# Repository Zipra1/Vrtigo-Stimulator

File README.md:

# This project is very very new, there is like. nothing here yet. Come back later?
GVS stimulation device, primarily for use in Virtual Reality applications (such as VRChat) to provide a sense of movement when you are moved in the game. Could also theoretically be used to reduce motion sickness, but the main goal is haptics.
Eventually, there will be two more repos: `Vertigo-Receiver` and `Vertigo-Server`

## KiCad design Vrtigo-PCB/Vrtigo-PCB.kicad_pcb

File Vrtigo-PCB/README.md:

Schematic from [gururise](https://github.com/gururise/mind_control/blob/main/schematics/schematic.png) for now.

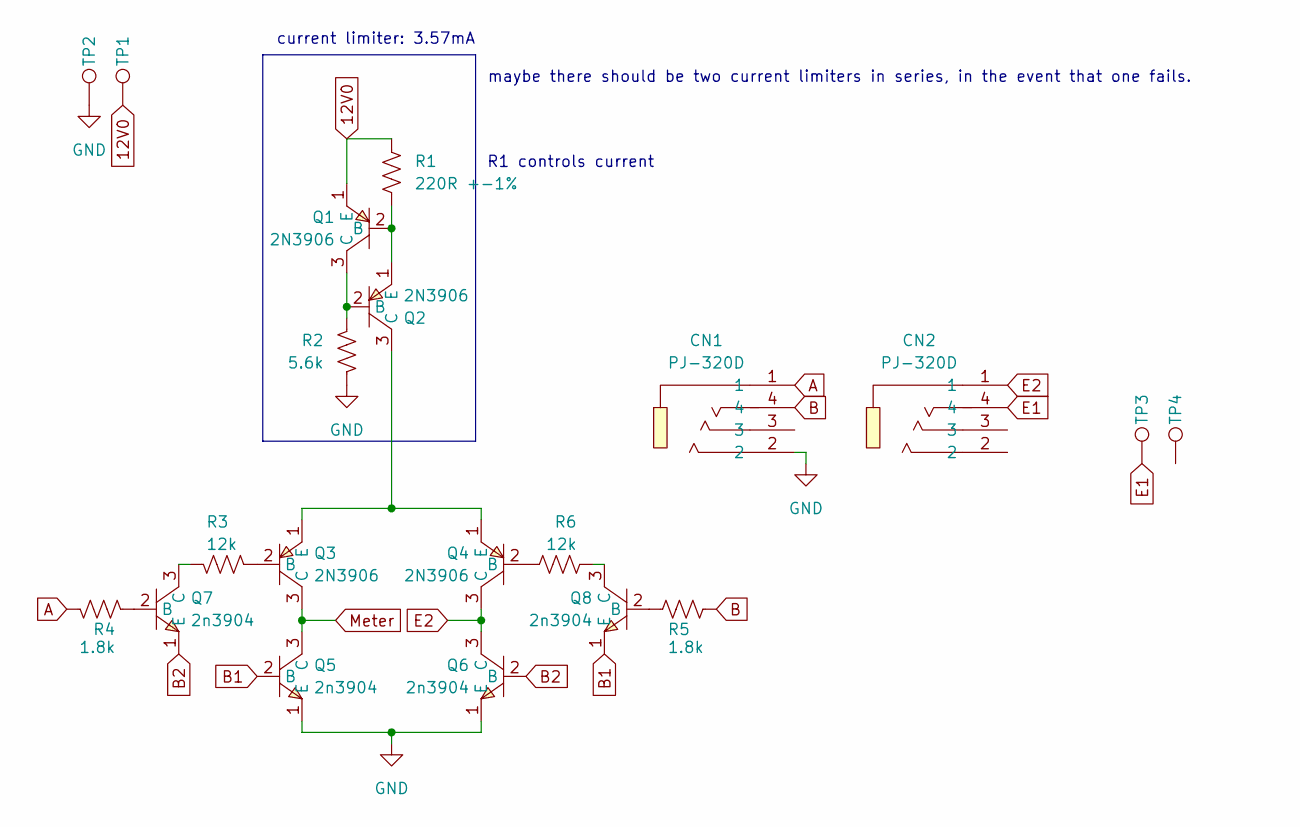
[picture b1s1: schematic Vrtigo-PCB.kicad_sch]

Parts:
CN1, CN2: PJ-320D; AUDIO-SMD_PJ-320D; LCSC Part C431535
Q1, Q2, Q3, Q4: 2N3906; SOT-23-3_L2.9-W1.3-P1.90-LS2.4-TR; LCSC Part C5300004
Q5, Q6, Q7, Q8: 2n3904; SOT-23-3_L2.9-W1.3-P1.90-LS2.4-TR; LCSC Part C18536
R1: 220R +-1%; R_0402_JLC
R2: 5.6k; R_0402_JLC
R3, R6: 12k; R_0402_JLC
R4, R5: 1.8k; R_0402_JLC
TP1, TP2, TP3, TP4: 2_3-1.5_2.5_1_1

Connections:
12V0: Q1.1 (E), R1.1, TP1.1
A: CN1.1, R4.2
B: CN1.4, R5.2
B1: Q5.2 (B), Q8.1 (E)
B2: Q6.2 (B), Q7.1 (E)
E1: CN2.4, TP3.1
E2: CN2.1, Q4.3 (C), Q6.3 (C)
GND: CN1.2, Q5.1 (E), Q6.1 (E), R2.1, TP2.1
Meter: Q3.3 (C), Q5.3 (C), TP4.1
unnamed: Q1.2 (B), Q2.1 (E), R1.2
unnamed: Q1.3 (C), Q2.2 (B), R2.2
unnamed: Q2.3 (C), Q3.1 (E), Q4.1 (E)
unnamed: Q3.2 (B), R3.2
unnamed: Q4.2 (B), R6.2
unnamed: Q7.2 (B), R4.1
unnamed: Q7.3 (C), R3.1
unnamed: Q8.2 (B), R5.1
unnamed: Q8.3 (C), R6.1

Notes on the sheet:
current limiter: 3.57mA
maybe there should be two current limiters in series, in the event that one fails.
R1 controls current

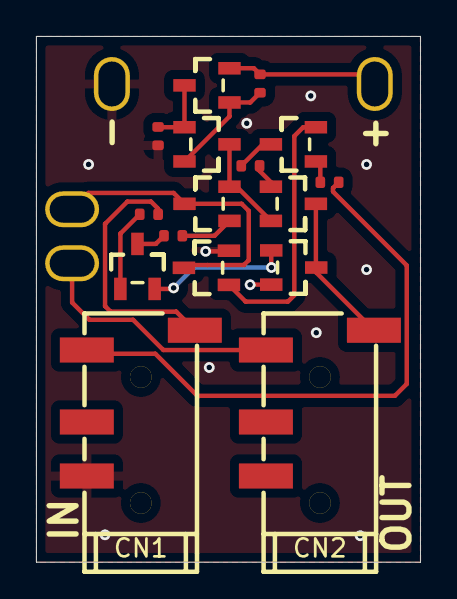
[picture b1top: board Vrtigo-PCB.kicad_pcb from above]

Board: 2 copper layers, 21.3 x 29.2 mm, 20 parts (0 on the bottom side), 18 nets.

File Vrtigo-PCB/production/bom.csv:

Designator,Footprint,Quantity,Value,LCSC Part #
"CN1, CN2",AUDIO-SMD_PJ-320D,2,PJ-320D,C431535
"Q1, Q2, Q3, Q4",SOT-23-3_L2.9-W1.3-P1.90-LS2.4-TR,4,2N3906,C5300004
"Q5, Q6, Q7, Q8",SOT-23-3_L2.9-W1.3-P1.90-LS2.4-TR,4,2n3904,C18536
R1,R_0402_JLC,1,220R +-1%,
R2,R_0402_JLC,1,5.6k,
"R3, R6",R_0402_JLC,2,12k,
"R4, R5",R_0402_JLC,2,1.8k,
"TP1, TP2, TP3, TP4",2_3-1.5_2.5_1_1,4,~,

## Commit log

2025-08-10 Setup commit, added folder structure.
2025-08-10 - Created PCB
2025-08-10 - Improved PCB layout - Added PCB silkscreen
